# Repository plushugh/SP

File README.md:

# **INFO: This repo is now archived, it contains science fair projects done before 2020**

# SP
Science Projects

## project one 
* created at 2018/12/22
* classroom-data reporter
* code-name: controler
## project two
* created at 2019/12
* dog care car
* code-name: carcontrols
## Versioning
* 1.0.0-xxxx
* First digit: main version
* Secone digit: Code version
* Third digit: PCB version
* -xxxx part: Pre-release Tag

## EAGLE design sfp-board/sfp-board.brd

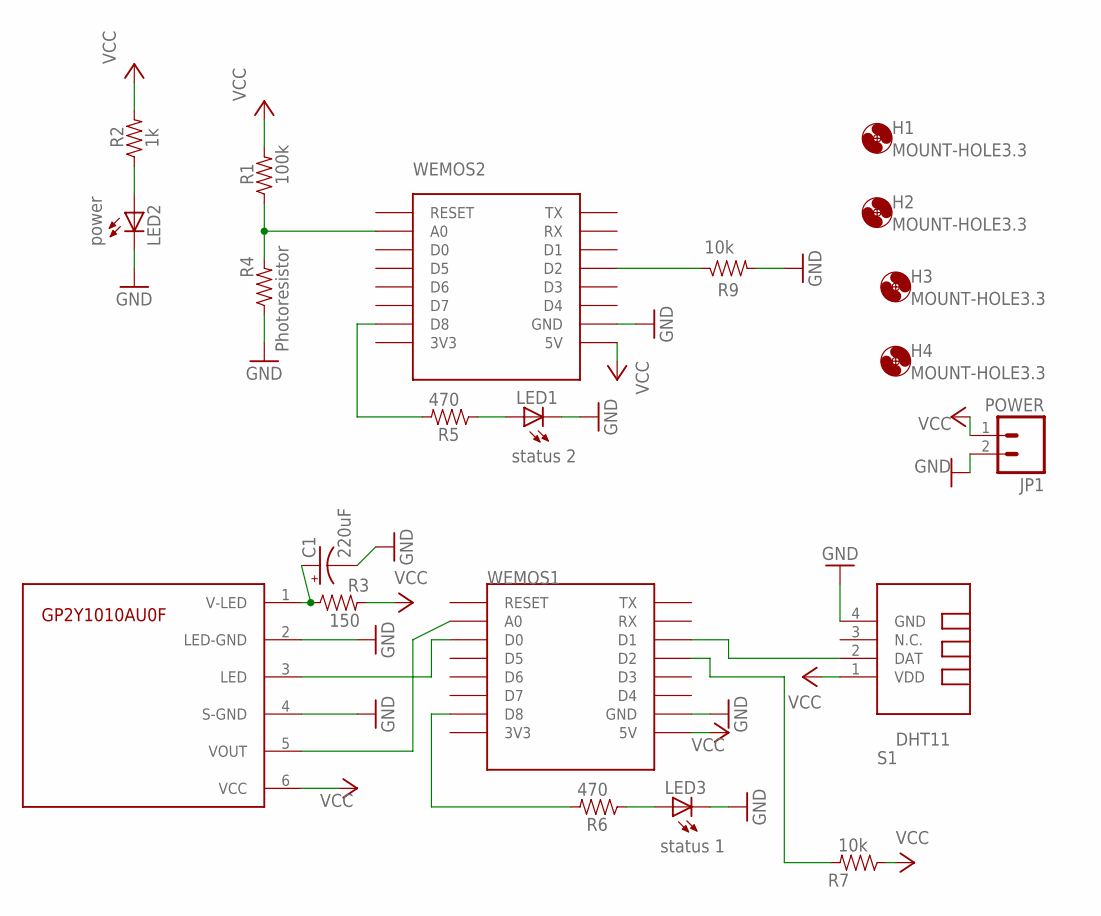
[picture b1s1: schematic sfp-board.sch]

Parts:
C1: 220uF; CPOL-RADIAL-100UF-25V
GP2Y1010AU0F: GP2Y1010AU
H1, H2, H3, H4: MOUNT-HOLE3.3; 3,3
JP1: POWER; 1X02_LONGPADS
LED1: status 2; LED5MM
LED2: power; LED5MM
LED3: status 1; LED5MM
R1: 100k; 0414/15
R2: 1k; 0414/15
R3: 150; 0414/15
R4: Photoresistor; 0414V
R5, R6: 470; 0414/15
R7, R9: 10k; 0414/15
S1: DHT11; TEMP-HUM-SENSOR-DHT11
U$1: BRS-SYMBOL; BRS
WEMOS1, WEMOS2: WEMOS-D1-MINI

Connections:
GND: C1.2 (-), GP2Y1010AU0F.2 (LED-GND), GP2Y1010AU0F.4 (S-GND), JP1.2, LED1.K (C), LED2.K (C), LED3.K (C), R4.1, R9.2, S1.4 (GND), WEMOS1.GND, WEMOS2.GND
unnamed: C1.1 (+), GP2Y1010AU0F.1 (V-LED), R3.1
unnamed: R1.1, R4.2, WEMOS2.A0
unnamed: GP2Y1010AU0F.3 (LED), WEMOS1.D0
unnamed: GP2Y1010AU0F.5 (VOUT), WEMOS1.A0
unnamed: LED2.A, R2.1
unnamed: LED1.A, R5.1
unnamed: S1.2 (DAT), WEMOS1.D1
unnamed: LED3.A, R6.1
unnamed: R6.2, WEMOS1.D8
unnamed: R5.2, WEMOS2.D8
unnamed: R9.1, WEMOS2.D2
unnamed: R7.2, WEMOS1.D2
VCC: GP2Y1010AU0F.6 (VCC), JP1.1, R1.2, R2.2, R3.2, R7.1, S1.1 (VDD), WEMOS1.5V, WEMOS2.5V

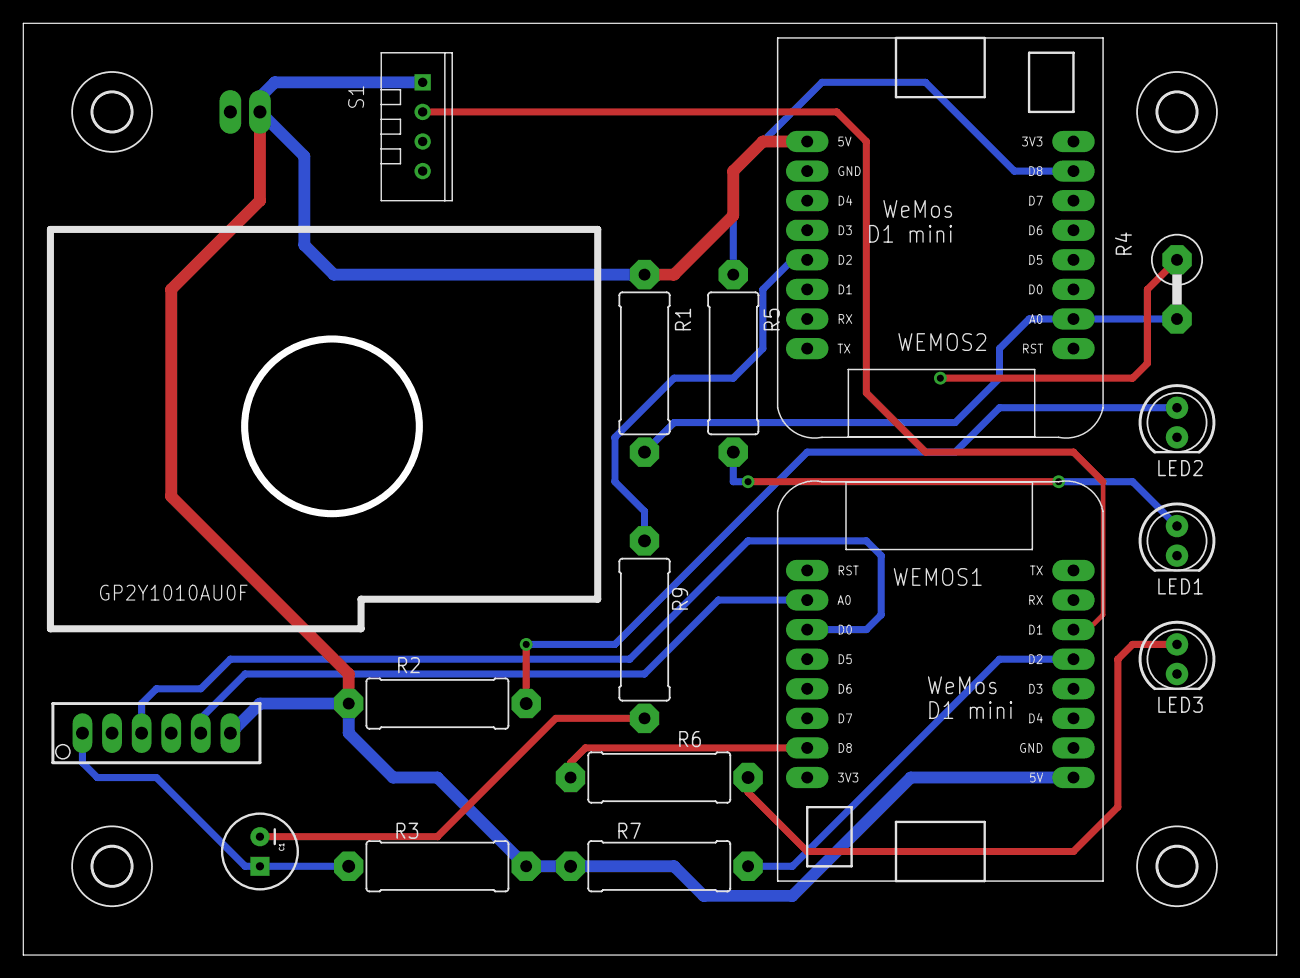
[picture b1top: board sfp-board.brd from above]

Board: 2 copper layers, 107.6 x 80.0 mm, 22 parts (0 on the bottom side), 14 nets.

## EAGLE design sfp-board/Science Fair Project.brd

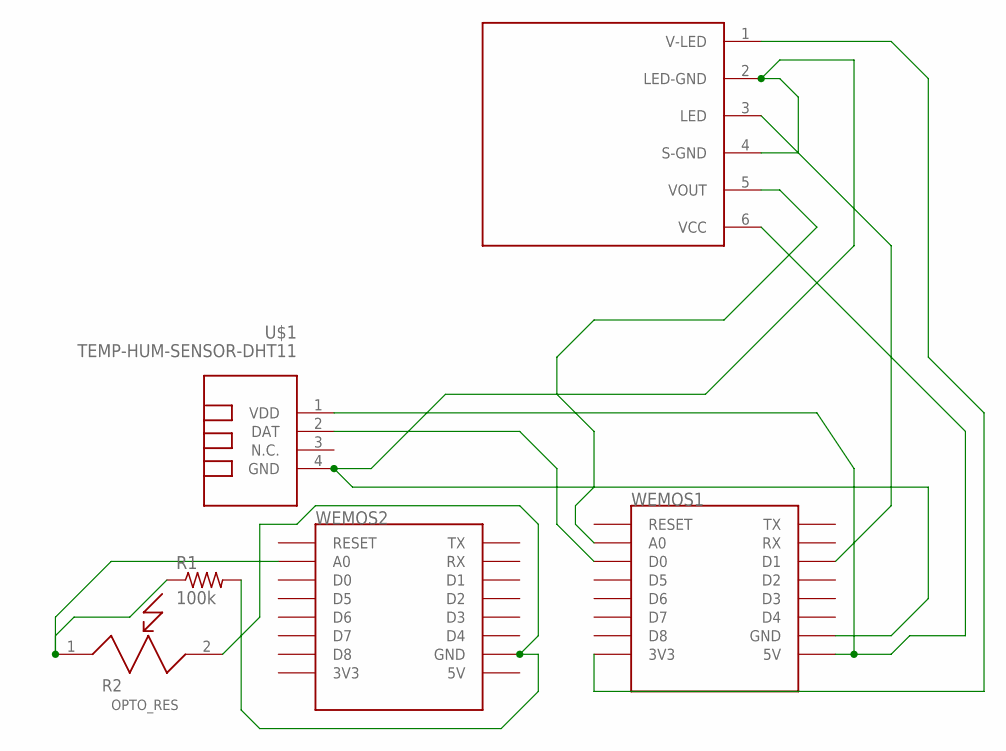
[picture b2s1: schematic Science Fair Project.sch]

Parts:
R1: 100k; 0411/15
R2: OPTO_RES
U$1: TEMP-HUM-SENSOR-DHT11
U$2: GP2Y1010AU
WEMOS1, WEMOS2: WEMOS-D1-MINI

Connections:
unnamed: U$1.4 (GND), U$2.2 (LED-GND), U$2.4 (S-GND), WEMOS1.GND
unnamed: R1.2, R2.2, WEMOS2.GND
unnamed: U$1.2 (DAT), WEMOS1.D0
unnamed: U$2.1 (V-LED), WEMOS1.3V3
unnamed: U$2.5 (VOUT), WEMOS1.A0
unnamed: U$1.1 (VDD), U$2.6 (VCC), WEMOS1.5V
unnamed: U$2.3 (LED), WEMOS1.D1
unnamed: R1.1, R2.1, WEMOS2.A0

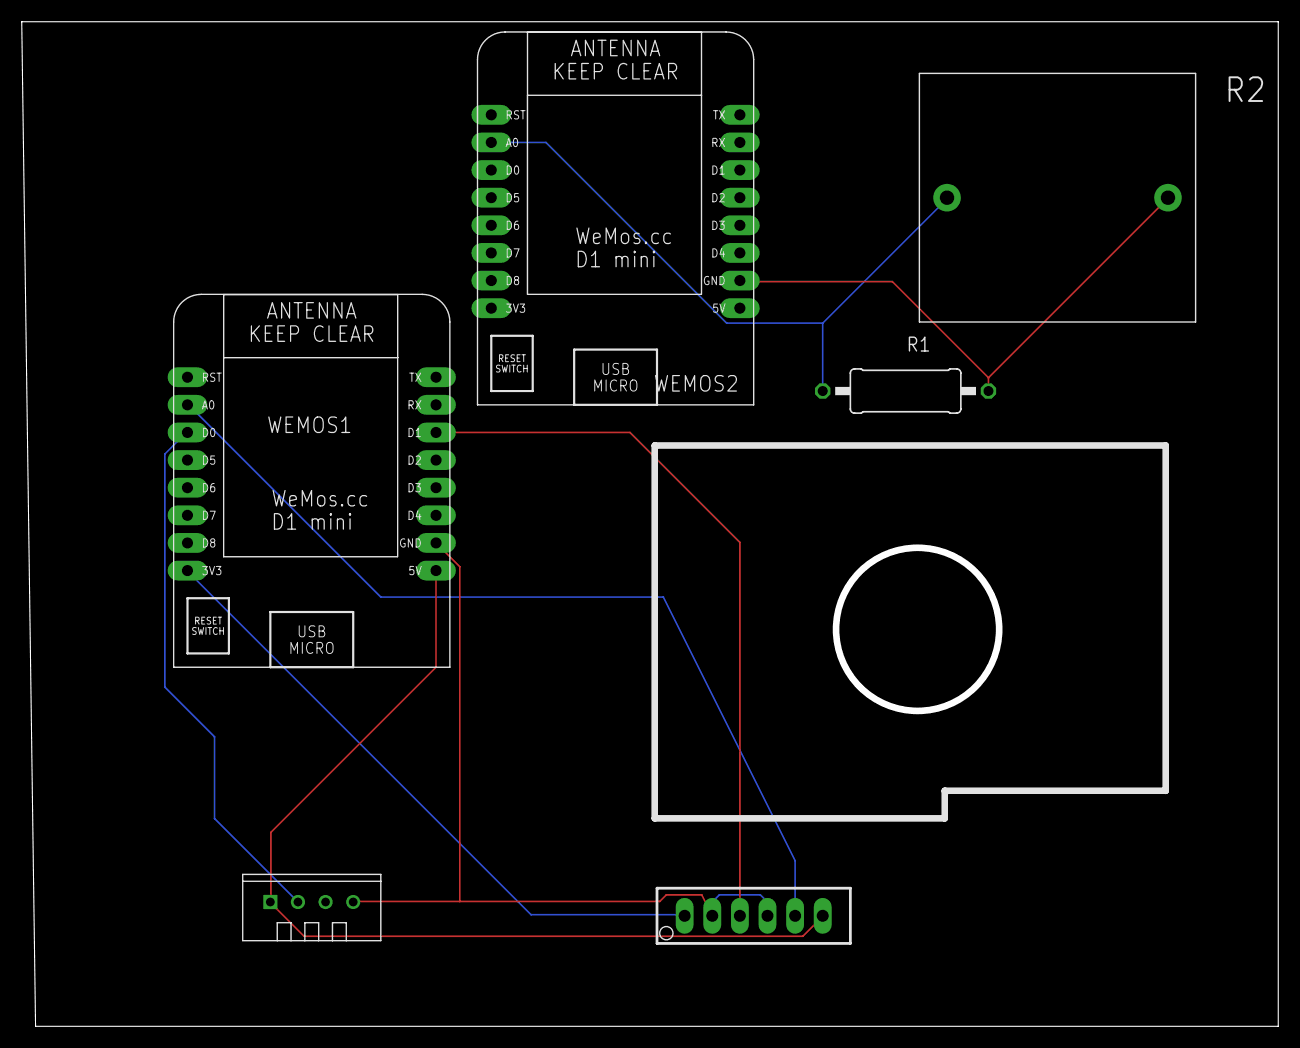
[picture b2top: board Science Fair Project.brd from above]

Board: 2 copper layers, 115.5 x 92.4 mm, 6 parts (0 on the bottom side), 8 nets.

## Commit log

2018-12-22 Update .gitignore
    ignore pyc
2018-12-22 Initial Arduino project for esp8266 cpu
2018-12-23 contoler demo version
2018-12-24 Science Fair board
2018-12-25 Add files via upload
    .brd of .sch
2018-12-25 board v2
2018-12-27 change folder
2018-12-28 Board v3
2019-01-06 Initial version sfp board
2019-01-06 add project file and lbr
2019-01-16 board V4
2019-01-17 board v5
2019-01-18 2019/1/10
    ignore the temprary files of eagle
2019-01-19 boardv6
2019-01-19 board v7
2019-01-20 board v8
2019-01-21 board v9
2019-01-22 board v10
2019-01-23 Set theme jekyll-theme-architect
2019-01-23 board with logo & update .gitgnore for ingoring tempoary file
2019-01-26 Added dust sensor reading program
2019-01-27 Board v13
2019-01-27 New gen of dust sensor reader
2019-01-29 board v14 with new dustsensor reader
2019-01-31 Board v15
2019-02-01 Board v16 with 4th Gen Code
2019-02-01 Board v17
2019-02-09 ReadDHT code and libs
2019-02-09 6th Gen assembled code
2019-02-09 dustsensorlib update (NOT a board update)
2019-02-11 board v18
2019-02-16 Set theme jekyll-theme-minimal
2019-02-17 Final board Arrangement #1
2019-02-17 Final board Arrangement #2
2019-02-17 Final board arrangement
2019-02-17 Final Board arrangement #4
2019-02-18 Final DRC: add version and process DRC error
2019-02-18 CAM version 1
2019-02-20 power on the status LED
2019-02-21 7th Gen assembled code
2019-02-21 8th Gen code
2019-04-08 Late Commit (ingore)
2019-08-31 RE-Arrange
2019-11-25 Arrange items while creating DogCar project
2019-12-07 Add UI
2019-12-07 [Dog Car]start UI app
2019-12-08 Finished UI
2019-12-08 fix spelling
2019-12-19 add setup()
2019-12-20 add shooter
2019-12-21 New UI + shooter & stop
2019-12-21 fix ui
2019-12-21 Add quit clean
2019-12-21 fix <10 bug

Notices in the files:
parts and their libraries:
diy-modules: Released under the Creative Commons Attribution 4.0 International License: http://creativecommons.org/licenses/by/4.0
SparkFun: Licensing: CC v3.0 Share-Alike You are welcome to use this library for commercial purposes.
